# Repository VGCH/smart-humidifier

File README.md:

# Модуль для управления увлажнителем с возможностью интеграции в Home Assistant

Разработан для увлажнителей Deerma Humidifier DEM-F628S / DEXP HD-440

## Скриншот автоматического определения устройства с помощью MQTT Auto Discovery 

## Полное описание проекта смотрите на Хабре

- [Описание проекта](https://habr.com/ru/articles/785252/)

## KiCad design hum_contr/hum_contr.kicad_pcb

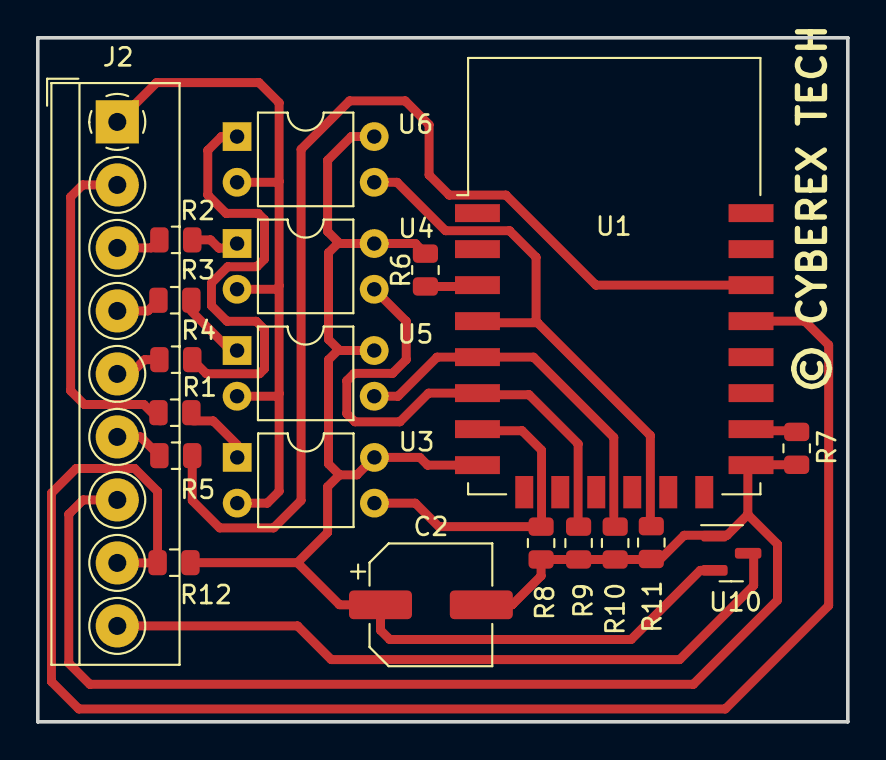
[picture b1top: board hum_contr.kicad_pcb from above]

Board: 2 copper layers, 45.0 x 38.0 mm, 20 parts (0 on the bottom side), 21 nets.

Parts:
C2: 200uF; CP_Elec_6.3x4.9
J2: TerminalBlock_4Ucon_1x09_P3.50mm_Horizontal
R1, R2, R3, R4, R5, R7: 100; R_0805_2012Metric
R6: 1к; R_0805_2012Metric
R8, R9, R10, R11: 125к; R_0805_2012Metric
R12: 4.7к; R_0805_2012Metric
U1: ESP-12E
U3, U4, U5, U6: EL817; DIP-4_W7.62mm
U10: HT7333; SOT-23

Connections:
GND: C2.2, J2.7, R7.1, R8.2, R9.2, R10.2, R11.2, U1.15 (GND), U10.1 (GND)
unnamed: J2.1, U3.2, U4.2, U5.2, U6.2
unnamed: J2.2, R1.1
unnamed: J2.3, R2.1
unnamed: J2.4, R3.1
unnamed: J2.5, R4.1
unnamed: J2.6, R5.2
unnamed: J2.8, R12.1, U1.19 (GPIO4)
unnamed: J2.9, U10.2 (VIN)
unnamed: R1.2, U3.1
unnamed: R2.2, U4.1
unnamed: R3.2, U5.1
unnamed: R4.2, U6.1
unnamed: R6.1, U1.3 (EN)
unnamed: R5.1, U1.20 (GPIO5)
unnamed: R9.1, U1.6 (GPIO12), U4.3
unnamed: R8.1, U1.7 (GPIO13), U3.3
unnamed: R10.1, U1.5 (GPIO14), U5.3
unnamed: R7.2, U1.16 (GPIO15)
unnamed: R11.1, U1.4 (GPIO16), U6.3
VCC: C2.1, R6.2, R12.2, U1.8 (VCC), U3.4, U4.4, U5.4, U6.4, U10.3 (VOUT)

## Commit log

2025-03-09 add function plug & play
2025-03-09 Add plug&play function
2025-03-09 Add images

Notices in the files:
hum_contr/hum_contr.kicad_pcb:
© CYBEREX TECH
